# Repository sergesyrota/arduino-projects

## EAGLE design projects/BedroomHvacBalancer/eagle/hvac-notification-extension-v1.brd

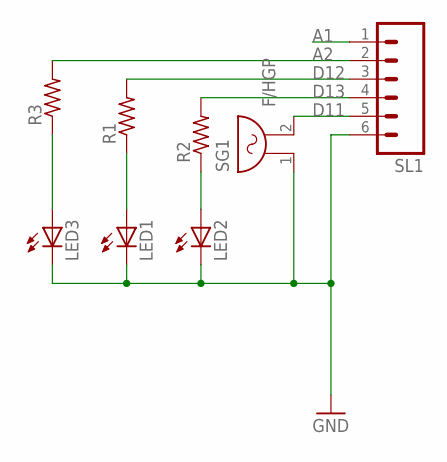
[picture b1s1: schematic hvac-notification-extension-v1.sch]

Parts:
LED1, LED2, LED3: LED3MM
R1, R2, R3: R-US_R0603; R0603
SG1: F/HGP
SL1: M06; 06P

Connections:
A1: SL1.1
A2: R3.2, SL1.2
D11: SG1.2, SL1.5
D12: R1.2, SL1.3
D13: R2.2, SL1.4
GND: LED1.K (C), LED2.K (C), LED3.K (C), SG1.1, SL1.6
unnamed: LED2.A, R2.1
unnamed: LED1.A, R1.1
unnamed: LED3.A, R3.1

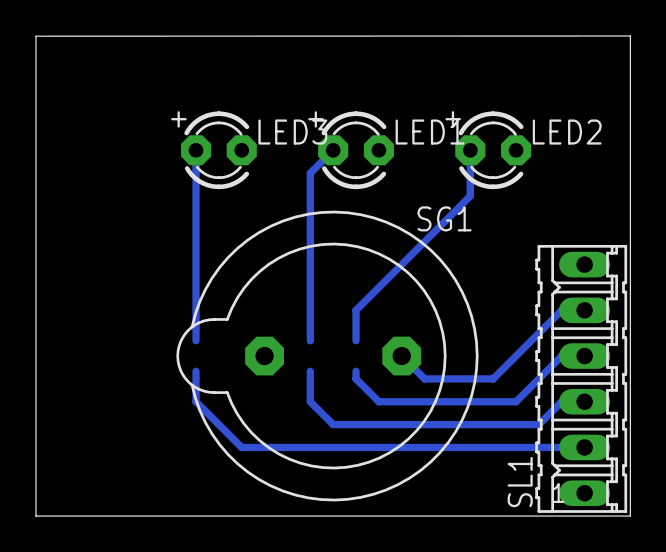
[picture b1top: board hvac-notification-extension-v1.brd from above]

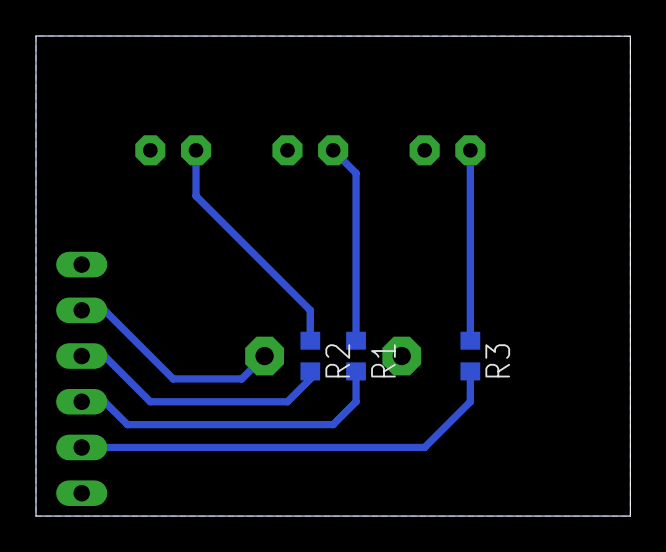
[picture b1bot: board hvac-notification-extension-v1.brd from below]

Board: 2 copper layers, 33.0 x 26.7 mm, 8 parts (3 on the bottom side), 8 nets.

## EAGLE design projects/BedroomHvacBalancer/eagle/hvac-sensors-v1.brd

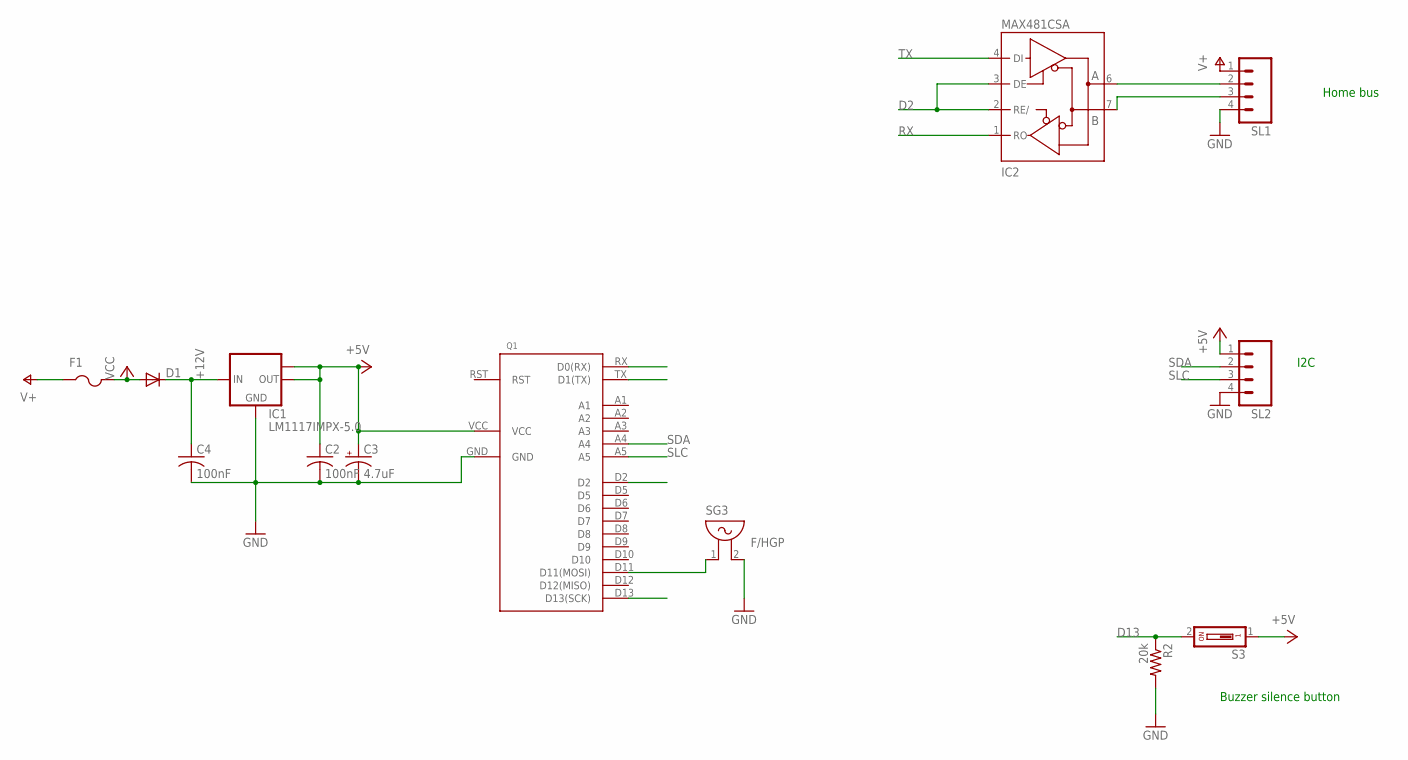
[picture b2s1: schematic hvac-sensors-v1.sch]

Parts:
C2, C4: 100nF; C0603K
C3: 4.7uF; E1,8-4
D1: DIODE-MICROMELF-W; MICROMELF-W
F1: PTCFUSE-1812; 1812
IC1: LM1117IMPX-5.0; SOT223
IC2: MAX481CSA; SO08
Q1: HOME-CPU-V1
R2: 20k; R0603
S3: DS01; DS-01
SG3: F/HGP
SL1, SL2: M04; 04P

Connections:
+12V: C4.1, D1.C, IC1.3 (IN)
D2: IC2.2 (RE/), IC2.3 (DE), Q1.D2
D13: Q1.D13 (D13(SCK)), R2.1, S3.2
GND: C2.2, C3.-, C4.2, IC1.1 (GND), IC2.5 (GND), Q1.GND, R2.2, SG3.2, SL1.4, SL2.4
unnamed: D1.A, F1.2
unnamed: Q1.D11 (D11(MOSI)), SG3.1
unnamed: IC2.6 (A), SL1.2
unnamed: IC2.7 (B), SL1.3
RX: IC2.1 (RO), Q1.RX (D0(RX))
SDA: Q1.A4, SL2.2
SLC: Q1.A5, SL2.3
TX: IC2.4 (DI), Q1.TX (D1(TX))
V+: F1.1, SL1.1
VCC: C2.1, C3.+, IC1.2 (OUT), IC1.TAB (OUT1), IC2.8 (VCC), Q1.VCC, S3.1, SL2.1

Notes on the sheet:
Buzzer silence button
Home bus
I2C

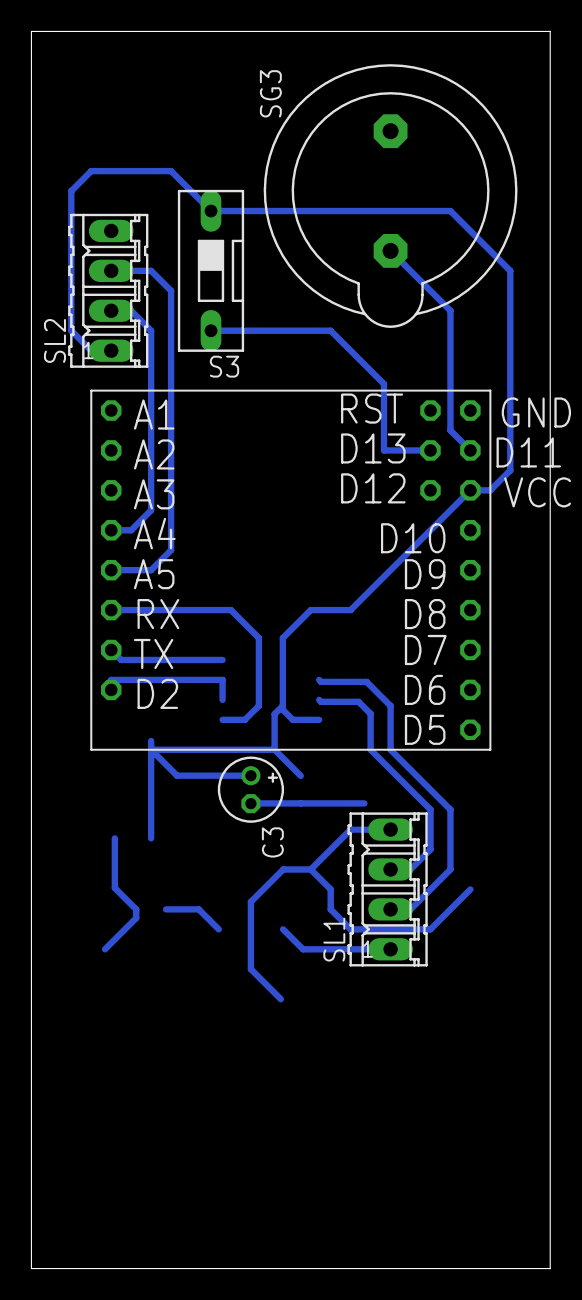
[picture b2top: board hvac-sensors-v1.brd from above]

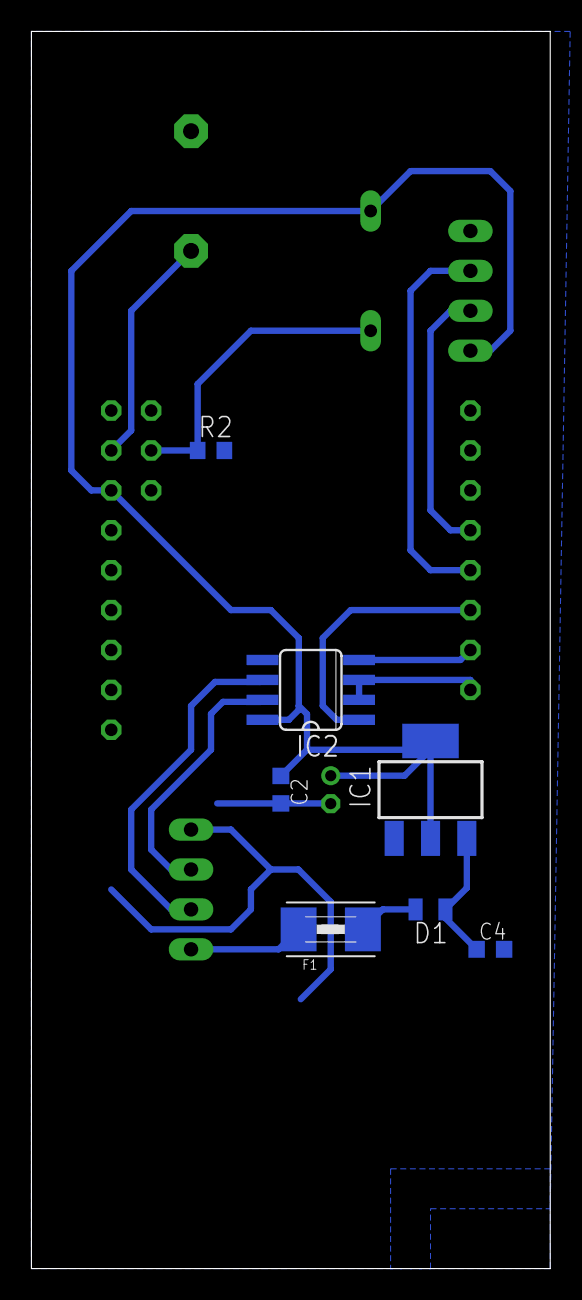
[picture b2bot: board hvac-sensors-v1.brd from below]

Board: 2 copper layers, 33.0 x 78.7 mm, 13 parts (7 on the bottom side), 14 nets.

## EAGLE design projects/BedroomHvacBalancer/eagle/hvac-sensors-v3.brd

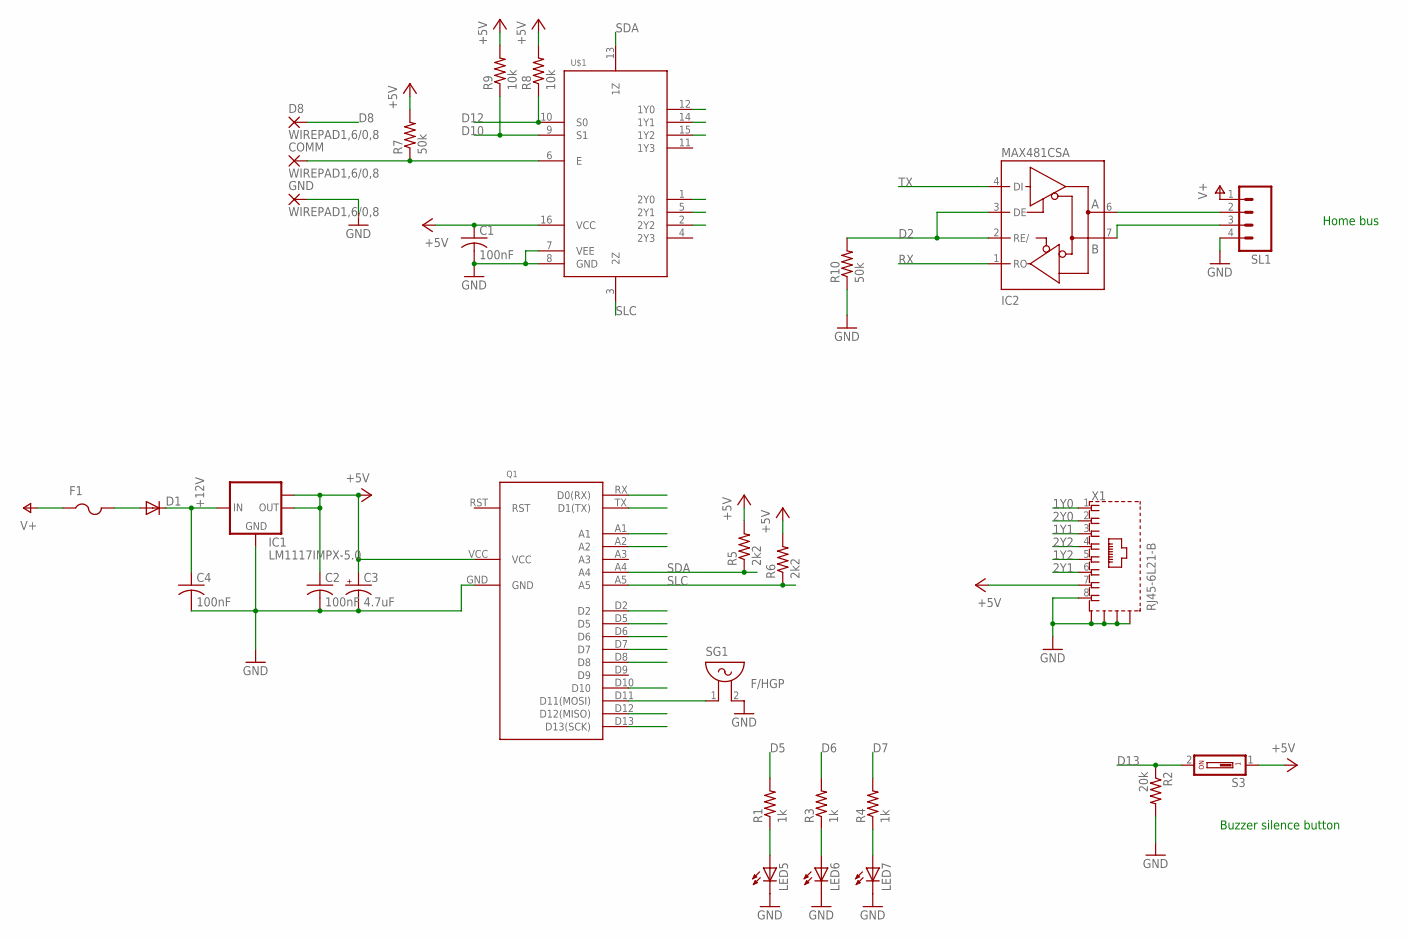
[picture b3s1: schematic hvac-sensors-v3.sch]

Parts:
C1, C2, C4: 100nF; C0603K
C3: 4.7uF; E1,8-4
COMM: WIREPAD1,6/0,8; 1,6/0,8
D1: DIODE-MICROMELF-W; MICROMELF-W
D8: WIREPAD1,6/0,8; 1,6/0,8
F1: PTCFUSE-1812; 1812
GND: WIREPAD1,6/0,8; 1,6/0,8
IC1: LM1117IMPX-5.0; SOT223
IC2: MAX481CSA; SO08
LED5, LED6, LED7: LED5MM
Q1: HOME-CPU-V1
R1, R3, R4: 1k; R0603
R2: 20k; R0603
R5, R6: 2k2; R0603
R7, R10: 50k; R0603
R8, R9: 10k; R0603
S3: DS01; DS-01
SG1: F/HGP
SL1: M04; 04P
U$1: 74HC4052SO-16; SO16
X1: RJ45-6L21-B; RJ45-SHIELD1

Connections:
1Y0: U$1.12 (1Y0), X1.1
1Y1: U$1.14 (1Y1), X1.3
1Y2: U$1.15 (1Y2), X1.5
2Y0: U$1.1 (2Y0), X1.2
2Y1: U$1.5 (2Y1), X1.6
2Y2: U$1.2 (2Y2), X1.4
+12V: C4.1, D1.C, IC1.3 (IN)
A1: Q1.A1
A2: Q1.A2
D2: IC2.2 (RE/), IC2.3 (DE), Q1.D2, R10.2
D5: Q1.D5, R1.2
D6: Q1.D6, R3.2
D7: Q1.D7, R4.2
D8: D8.1, Q1.D8
D10: Q1.D10, R9.1, U$1.9 (S1)
D11: Q1.D11 (D11(MOSI)), SG1.1
D12: Q1.D12 (D12(MISO)), R8.1, U$1.10 (S0)
D13: Q1.D13 (D13(SCK)), R2.1, S3.2
GND: C1.2, C2.2, C3.-, C4.2, GND.1, IC1.1 (GND), IC2.5 (GND), LED5.K (C), LED6.K (C), LED7.K (C), Q1.GND, R2.2, R10.1, SG1.2, SL1.4, U$1.7 (VEE), U$1.8 (GND), X1.8, X1.S1 (S), X1.S2 (S), X1.S3 (S), X1.S4 (S)
unnamed: D1.A, F1.2
unnamed: IC2.6 (A), SL1.2
unnamed: IC2.7 (B), SL1.3
unnamed: COMM.1, R7.1, U$1.6 (E)
unnamed: LED5.A, R1.1
unnamed: LED6.A, R3.1
unnamed: LED7.A, R4.1
RX: IC2.1 (RO), Q1.RX (D0(RX))
SDA: Q1.A4, R5.1, U$1.13 (1Z)
SLC: Q1.A5, R6.1, U$1.3 (2Z)
TX: IC2.4 (DI), Q1.TX (D1(TX))
V+: F1.1, SL1.1
VCC: C1.1, C2.1, C3.+, IC1.2 (OUT), IC1.TAB (OUT1), IC2.8 (VCC), Q1.VCC, R5.2, R6.2, R7.2, R8.2, R9.2, S3.1, U$1.16 (VCC), X1.7

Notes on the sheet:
Buzzer silence button
Home bus

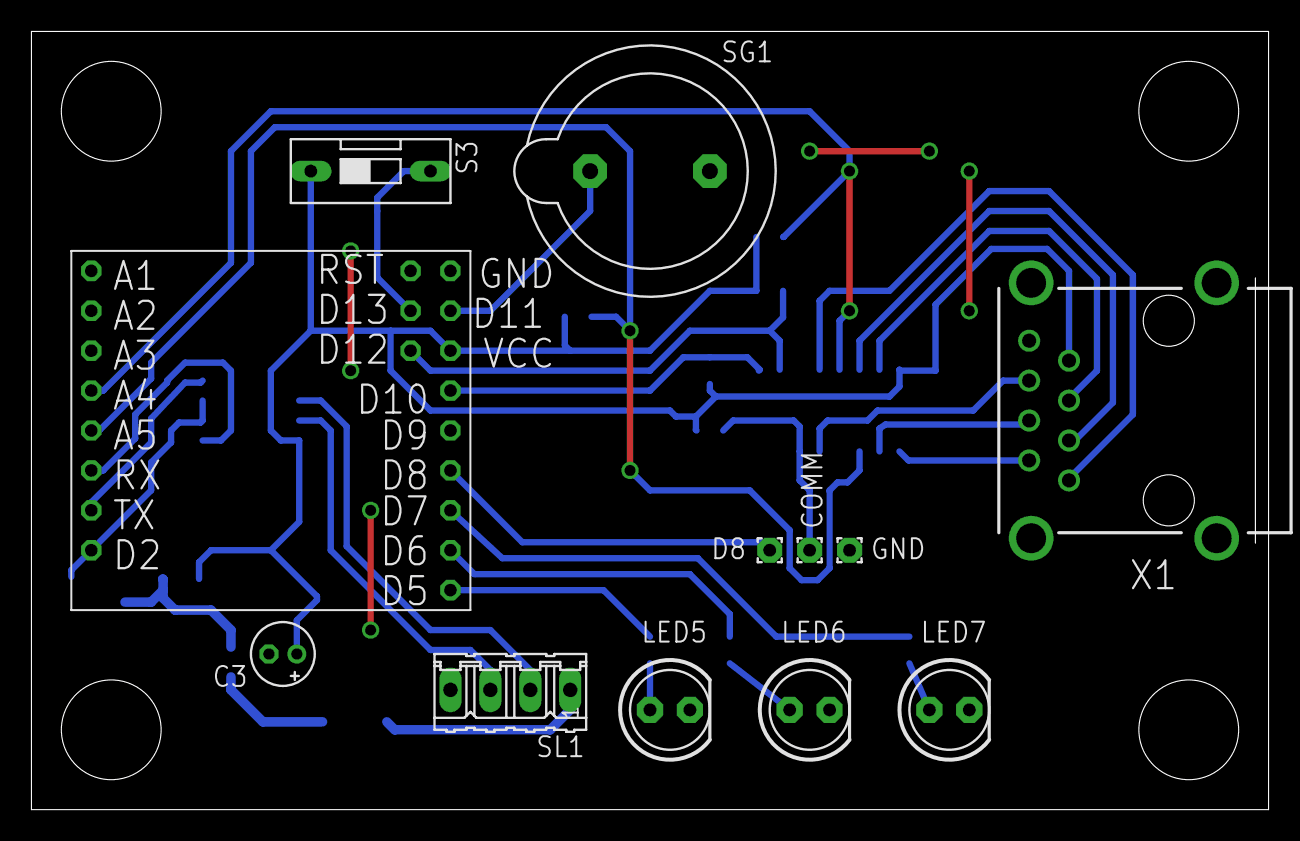
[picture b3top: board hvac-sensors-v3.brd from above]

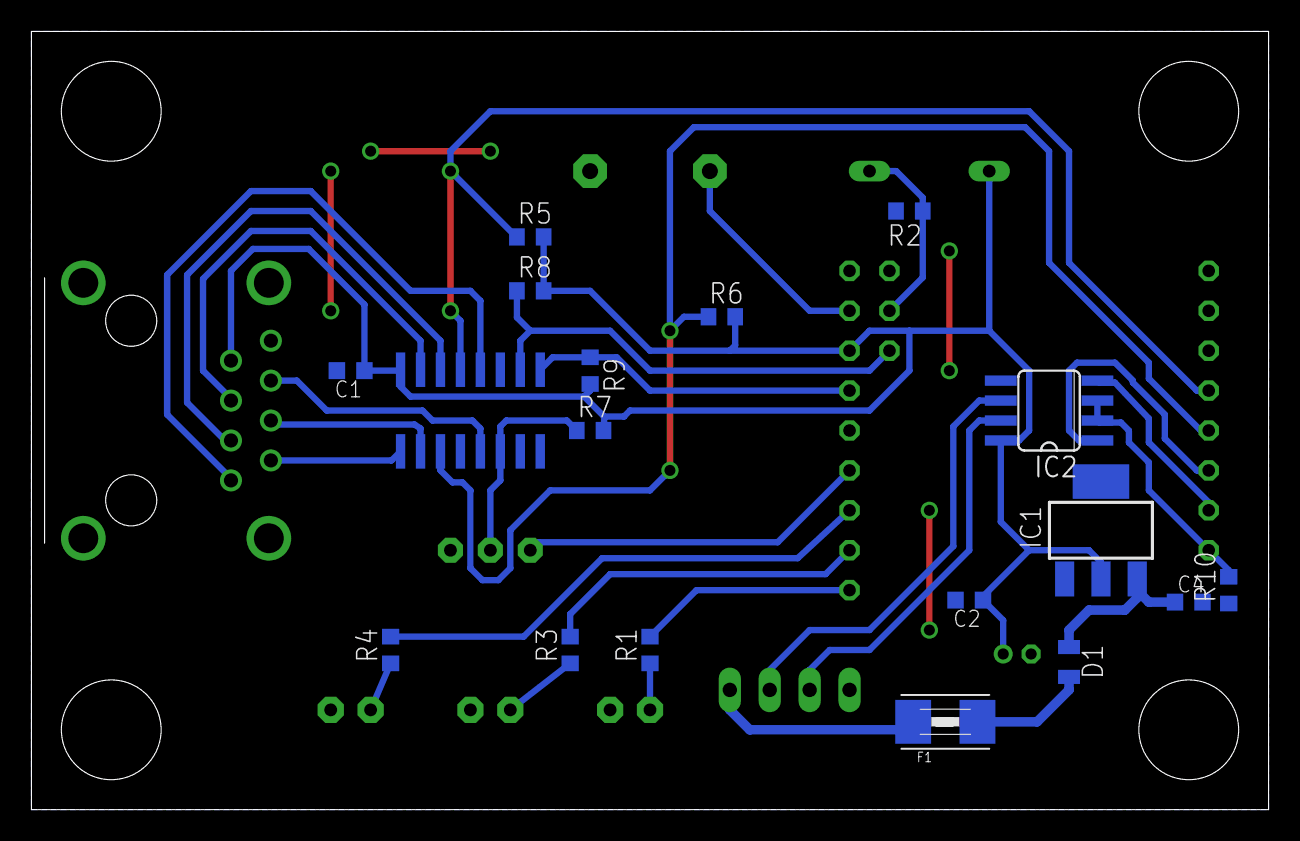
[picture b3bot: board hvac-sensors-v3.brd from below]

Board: 2 copper layers, 78.7 x 49.5 mm, 30 parts (18 on the bottom side), 30 nets.

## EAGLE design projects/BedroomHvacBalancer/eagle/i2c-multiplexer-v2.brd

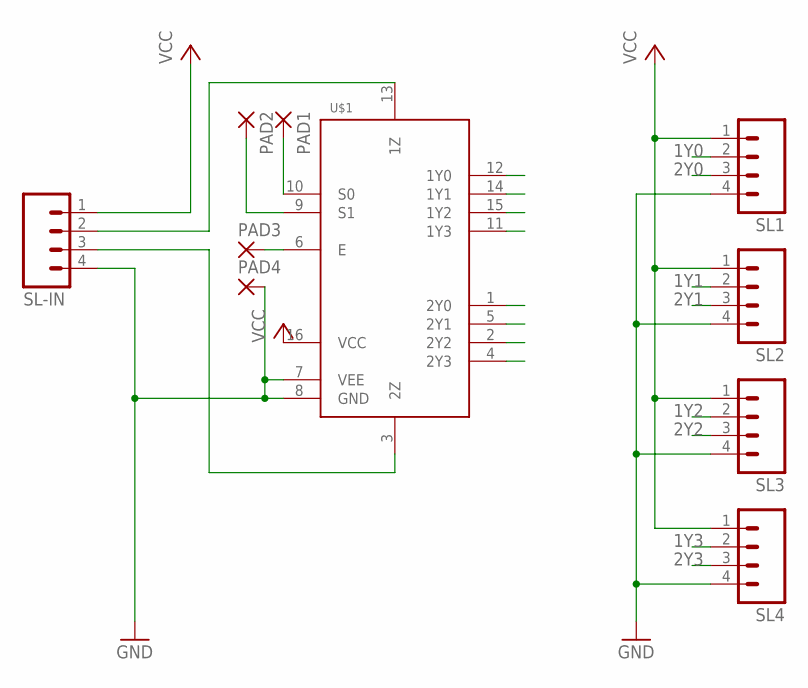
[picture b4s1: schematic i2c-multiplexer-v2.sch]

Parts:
PAD1, PAD2, PAD3, PAD4: 1,6/0,8
SL1, SL2, SL3, SL4: M04; 04P
SL-IN: M04; 04P
U$1: 74HC4052SO-16; SO16

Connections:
1Y0: SL1.2, U$1.12 (1Y0)
1Y1: SL2.2, U$1.14 (1Y1)
1Y2: SL3.2, U$1.15 (1Y2)
1Y3: SL4.2, U$1.11 (1Y3)
2Y0: SL1.3, U$1.1 (2Y0)
2Y1: SL2.3, U$1.5 (2Y1)
2Y2: SL3.3, U$1.2 (2Y2)
2Y3: SL4.3, U$1.4 (2Y3)
GND: PAD4.1, SL1.4, SL2.4, SL3.4, SL4.4, SL-IN.4, U$1.7 (VEE), U$1.8 (GND)
unnamed: SL-IN.2, U$1.13 (1Z)
unnamed: SL-IN.3, U$1.3 (2Z)
unnamed: PAD3.1, U$1.6 (E)
unnamed: PAD2.1, U$1.9 (S1)
unnamed: PAD1.1, U$1.10 (S0)
VCC: SL1.1, SL2.1, SL3.1, SL4.1, SL-IN.1, U$1.16 (VCC)

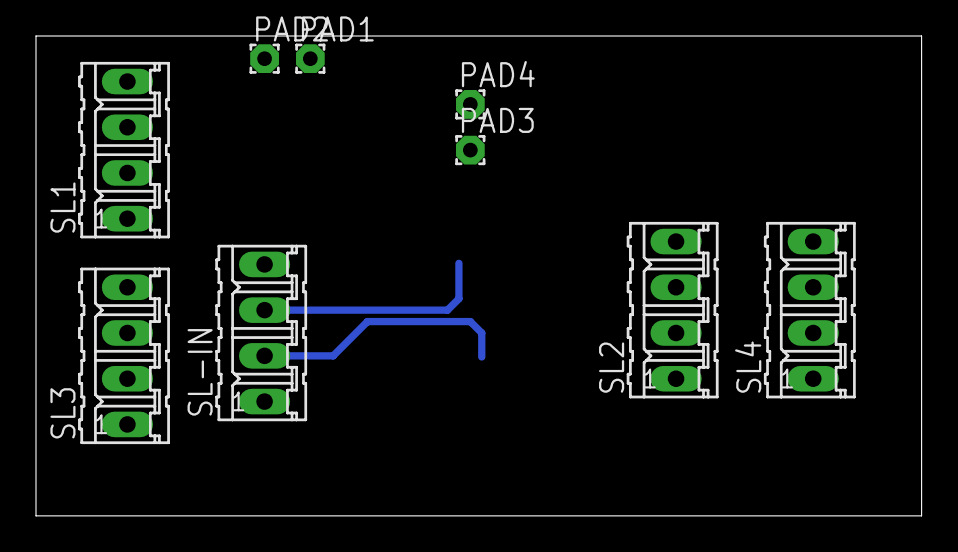
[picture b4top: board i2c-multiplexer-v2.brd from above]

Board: 2 copper layers, 49.2 x 26.7 mm, 10 parts (1 on the bottom side), 15 nets.

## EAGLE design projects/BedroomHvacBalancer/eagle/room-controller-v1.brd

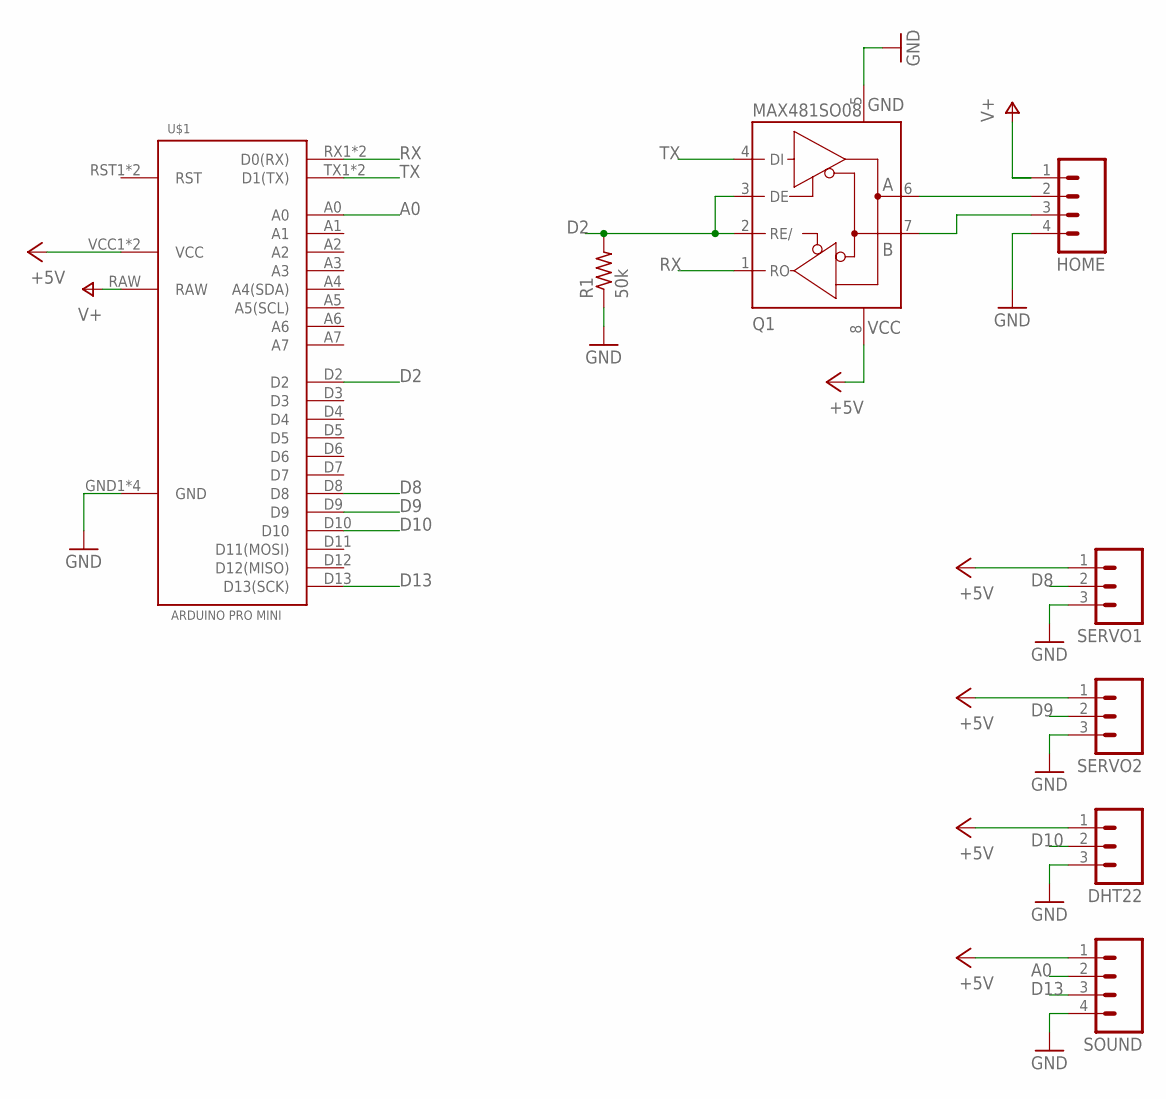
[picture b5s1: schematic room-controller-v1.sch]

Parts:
DHT22: M03; 03P
HOME: M04; 04P
Q1: MAX481SO08; SO08
R1: 50k; R0603
SERVO1, SERVO2: M03; 03P
SOUND: M04; 04P
U$1: ARDUINO-PRO-MINI

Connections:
+5V: DHT22.1, Q1.8 (+5V), SERVO1.1, SERVO2.1, SOUND.1, U$1.VCC1 (VCC), U$1.VCC2 (VCC)
A0: SOUND.2, U$1.A0
D2: Q1.2 (RE/), Q1.3 (DE), R1.2, U$1.D2
D8: SERVO1.2, U$1.D8
D9: SERVO2.2, U$1.D9
D10: DHT22.2, U$1.D10
D13: SOUND.3, U$1.D13 (D13(SCK))
GND: DHT22.3, HOME.4, Q1.5 (GND), R1.1, SERVO1.3, SERVO2.3, SOUND.4, U$1.GND1 (GND), U$1.GND2 (GND), U$1.GND3 (GND), U$1.GND4 (GND)
unnamed: HOME.2, Q1.6 (A)
unnamed: HOME.3, Q1.7 (B)
RX: Q1.1 (RO), U$1.RX1 (D0(RX)), U$1.RX2 (D0(RX))
TX: Q1.4 (DI), U$1.TX1 (D1(TX)), U$1.TX2 (D1(TX))
V+: HOME.1, U$1.RAW

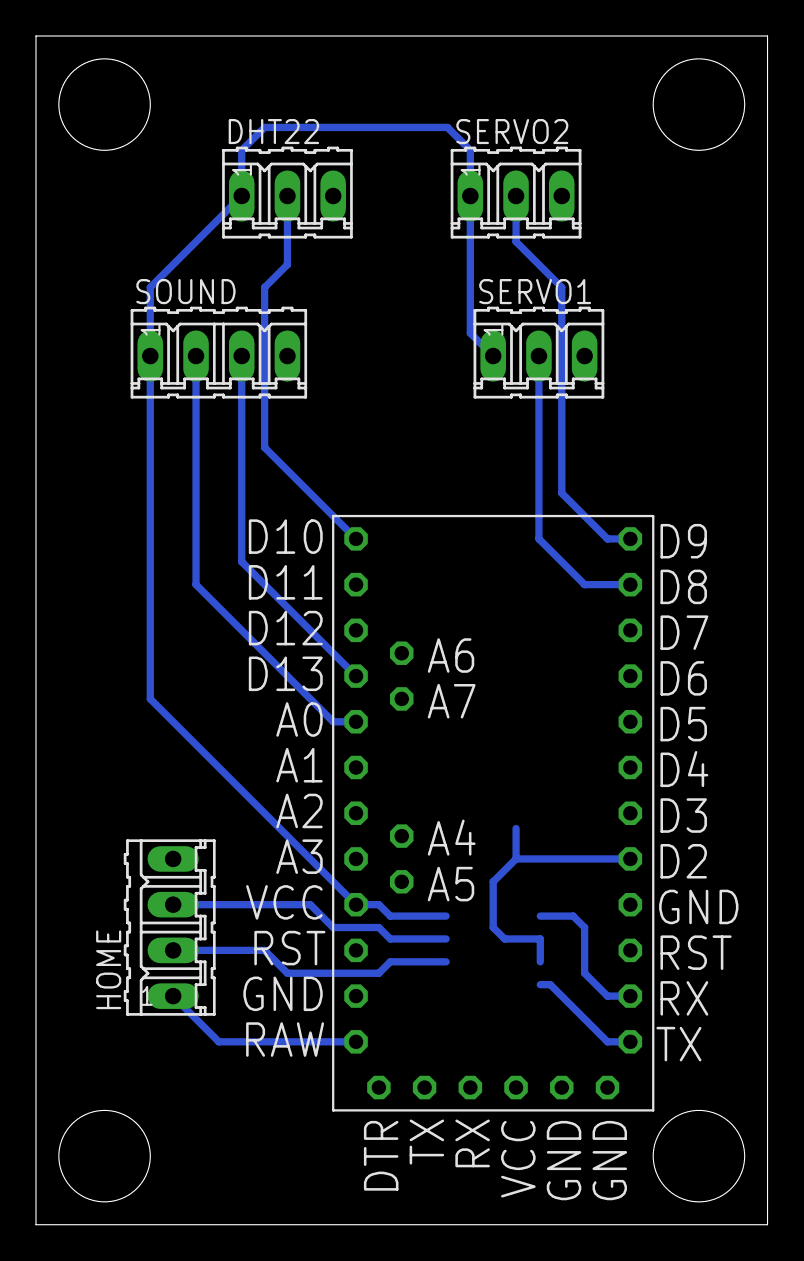
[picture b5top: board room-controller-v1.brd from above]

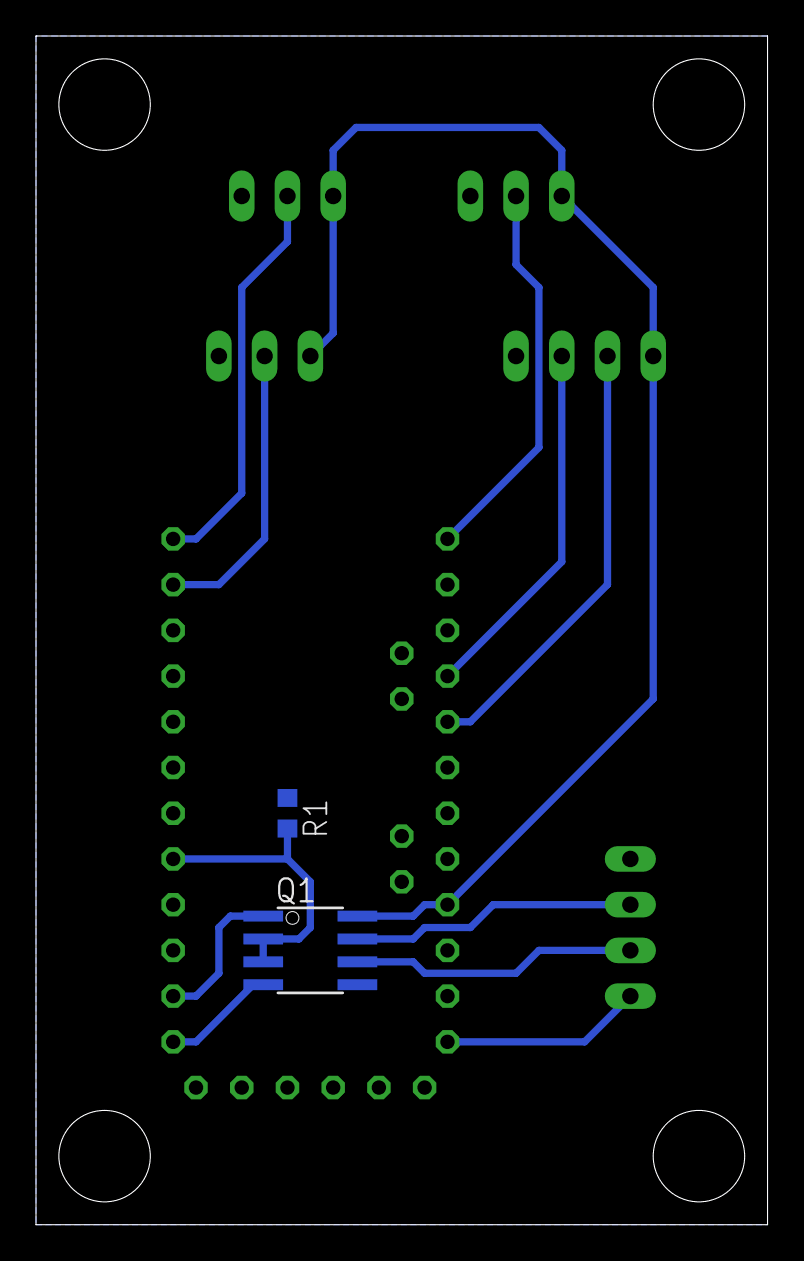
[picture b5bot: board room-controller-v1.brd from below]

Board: 2 copper layers, 40.6 x 66.0 mm, 8 parts (2 on the bottom side), 13 nets.

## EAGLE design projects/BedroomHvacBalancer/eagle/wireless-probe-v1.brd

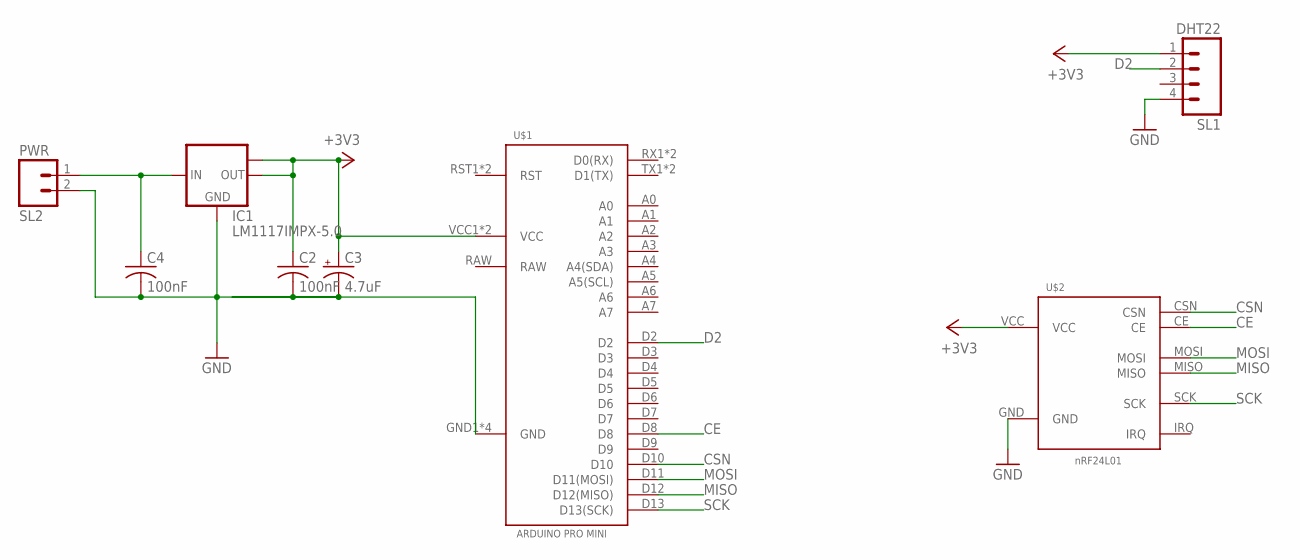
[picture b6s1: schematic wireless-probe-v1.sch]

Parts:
C2, C4: 100nF; C0603K
C3: 4.7uF; E1,8-4
IC1: LM1117IMPX-5.0; SOT223
SL1: DHT22; 04P
SL2: PWR; 02P
U$1: ARDUINO-PRO-MINI
U$2: NRF24L01MODULE; NRF24L01-MODULE

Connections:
+3V3: C2.1, C3.+, IC1.2 (OUT), IC1.TAB (OUT1), SL1.1, U$1.VCC1 (VCC), U$1.VCC2 (VCC), U$2.VCC
+12V: C4.1, IC1.3 (IN), SL2.1
CE: U$1.D8, U$2.CE
CSN: U$1.D10, U$2.CSN
D2: SL1.2, U$1.D2
GND: C2.2, C3.-, C4.2, IC1.1 (GND), SL1.4, SL2.2, U$1.GND1 (GND), U$1.GND2 (GND), U$1.GND3 (GND), U$1.GND4 (GND), U$2.GND
MISO: U$1.D12 (D12(MISO)), U$2.MISO
MOSI: U$1.D11 (D11(MOSI)), U$2.MOSI
RAW: U$1.RAW
SCK: U$1.D13 (D13(SCK)), U$2.SCK

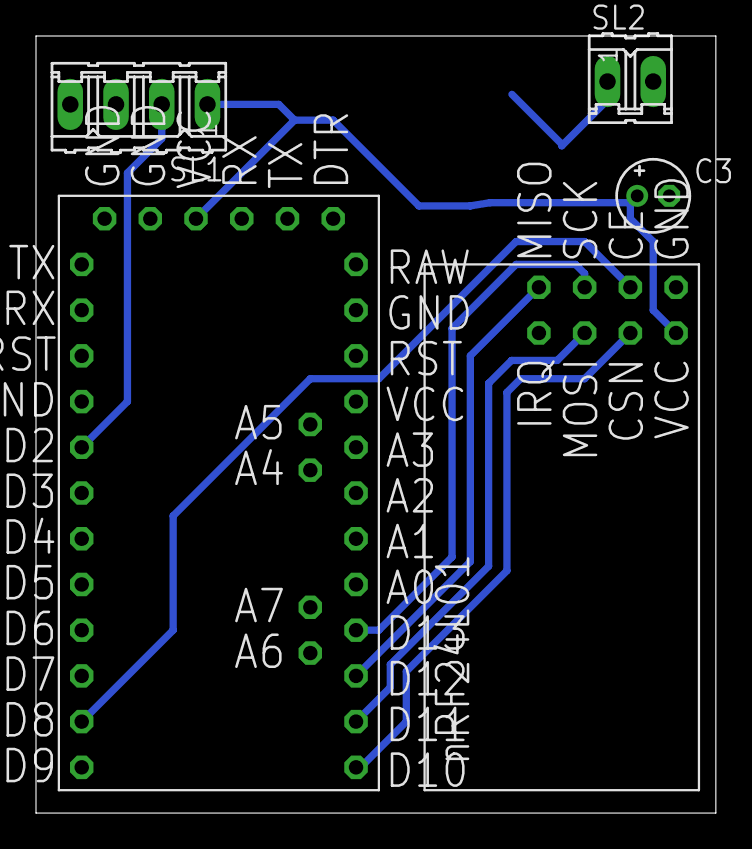
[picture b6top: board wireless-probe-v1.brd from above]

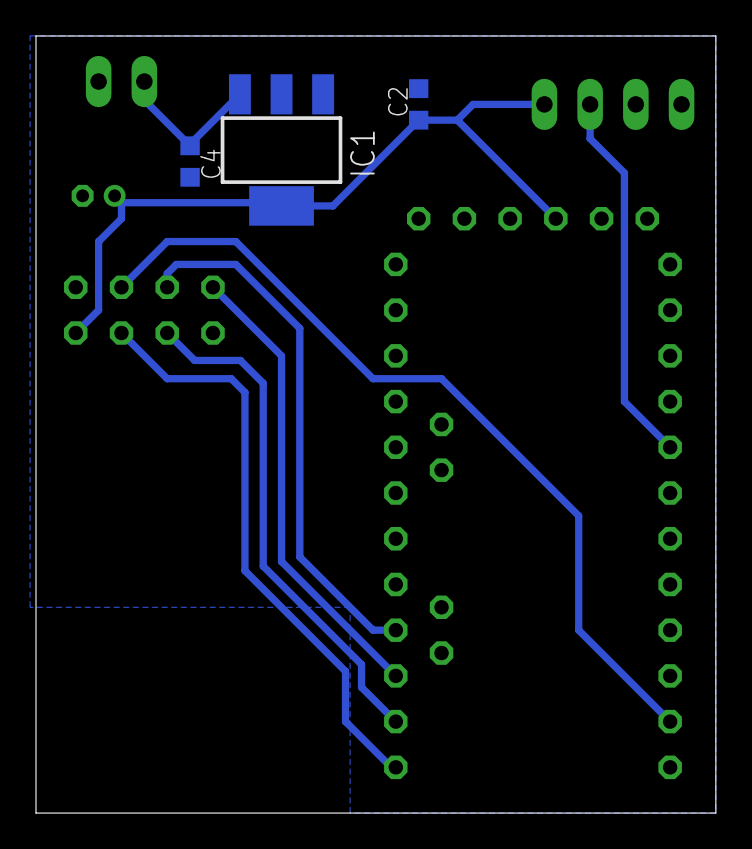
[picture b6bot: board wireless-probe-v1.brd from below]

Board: 2 copper layers, 37.8 x 43.2 mm, 8 parts (3 on the bottom side), 9 nets.

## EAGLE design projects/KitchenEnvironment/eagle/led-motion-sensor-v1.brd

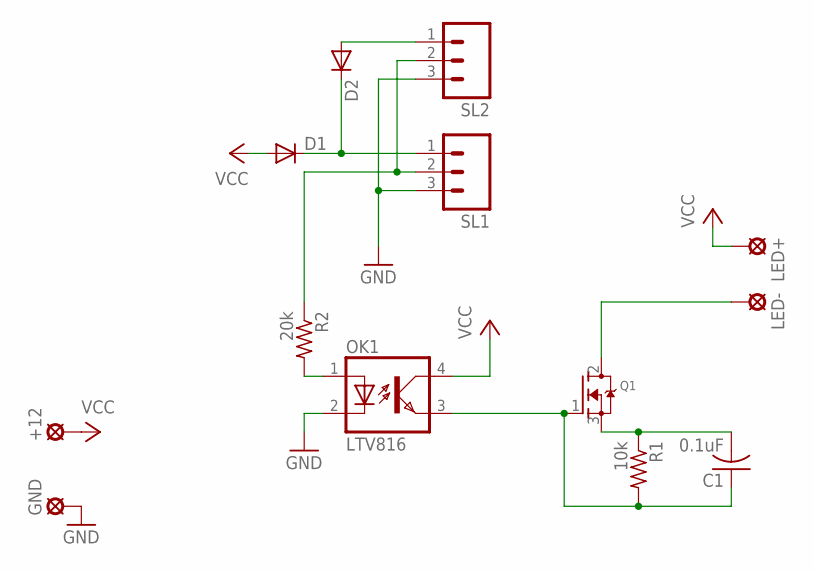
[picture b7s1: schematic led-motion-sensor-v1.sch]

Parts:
+12: LSP10
C1: 0.1uF; C0603K
D1, D2: DIODE-MICROMELF-W; MICROMELF-W
GND: LSP10
LED+: LSP10
LED-: LSP10
OK1: LTV816; DIL04
Q1: MOSFET-NGDS_TO220V; TO220V
R1: 10k; R0603
R2: 20k; R0603
SL1, SL2: M03; 03P

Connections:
GND: GND.MP, OK1.2 (C), SL1.3, SL2.3
unnamed: R2.1, SL1.2, SL2.2
unnamed: C1.1, OK1.3 (EMIT), Q1.1 (G), R1.2
unnamed: C1.2, Q1.3 (S), R1.1
unnamed: OK1.1 (A), R2.2
unnamed: LED-.MP, Q1.2 (D)
unnamed: D1.C, D2.C, SL1.1
unnamed: D2.A, SL2.1
VCC: +12.MP, D1.A, LED+.MP, OK1.4 (COL)

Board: 2 copper layers, 13 parts (0 on the bottom side), 9 nets, no tracks yet.
